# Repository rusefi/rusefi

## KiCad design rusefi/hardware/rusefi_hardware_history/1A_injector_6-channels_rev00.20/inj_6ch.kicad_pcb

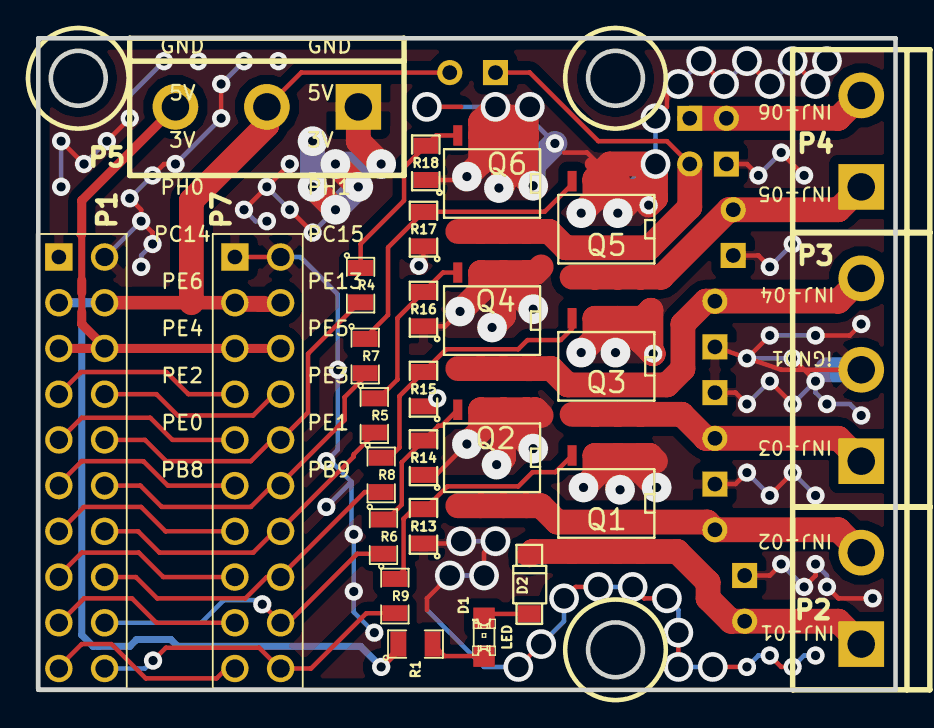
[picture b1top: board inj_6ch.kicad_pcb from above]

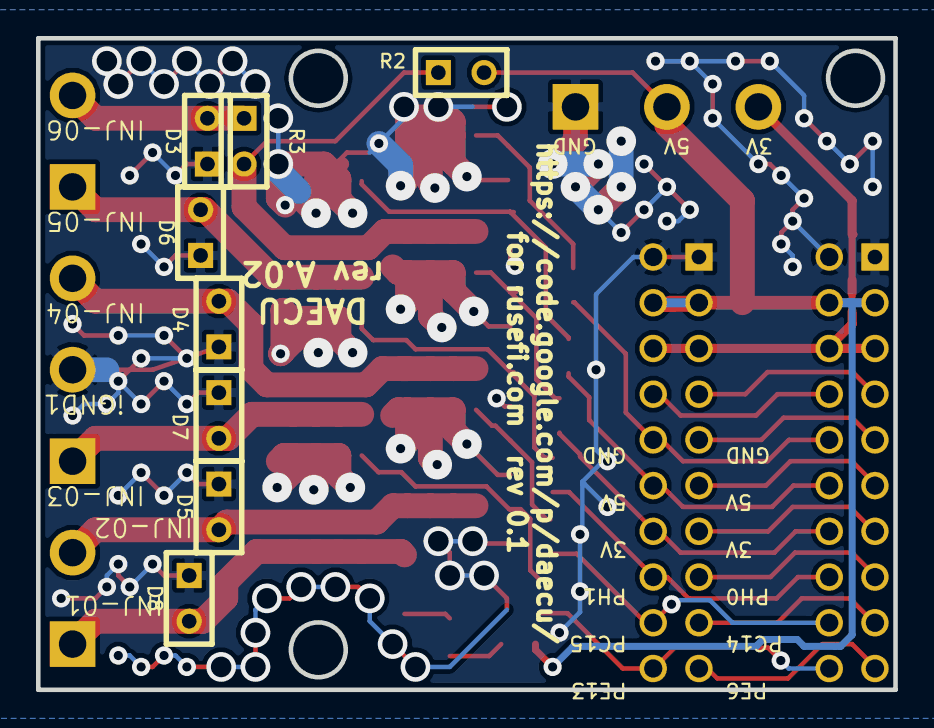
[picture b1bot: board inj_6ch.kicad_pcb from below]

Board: 2 copper layers, 47.6 x 36.2 mm, 35 parts (8 on the bottom side), 32 nets.

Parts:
D1: LED; LED-0805
D2: DIODE; SOD-123
D3, D4, D5, D6, D7, D8: DIODE; SIL-2
P1, P7: CONN_10X2; pin_array_10x2
P2, P4: CONN_2; bornier2
P3, P5: CONN_3; bornier3
Q1, Q2, Q3, Q4, Q5, Q6: OVP_DRIVER; SO8E_ST
R1, R13, R14, R15, R16, R17, R18: 1K; SM0805
R2: OPT; SIL-2
R3: 0R; SIL-2
R4, R5, R6, R7, R8, R9: 20R; SM0805

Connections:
/3V: P1.5, P1.6, P5.3, P7.5, P7.6
/5V: P1.3, P1.4, P5.2, P7.3, P7.4, R1.1, R2.2
/INJ-01: D2.2, D8.2, P2.1, Q1.2
/INJ-01_5V: P1.20, P7.20, R9.2
/INJ-02: D5.2, P2.2, Q2.2
/INJ-02_5V: P1.18, P7.18, R6.2
/INJ-03: D7.2, P3.1, Q3.2
/INJ-03_5V: P1.16, P7.16, R8.2
/INJ-04: D4.2, P3.3, Q4.2
/INJ-04_5V: P1.14, P7.14, R5.2
/INJ-05: D6.2, P4.1, Q5.2
/INJ-05_5V: P1.12, P7.12, R7.2
/INJ-06: Q6.2, R2.1, R3.2
/INJ-06_2: D3.2, P4.2, R3.1
/INJ-06_5V: P1.10, P7.10, R4.2
/PB8: P1.19, P7.19
/PC14: P1.9, P7.9
/PE0: P1.17, P7.17
/PE2: P1.15, P7.15
/PE4: P1.13, P7.13
/PE6: P1.11, P7.11
/PH0: P1.7, P7.7
/PH1: P1.8, P7.8
GND: D3.1, D4.1, D5.1, D6.1, D7.1, D8.1, P1.1, P1.2, P3.2, P5.1, P7.1, P7.2, Q1.3, Q2.3, Q3.3, Q4.3, Q5.3, Q6.3, R13.1, R14.1, R15.1, R16.1, R17.1, R18.1
unnamed: D1.1, R1.2
unnamed: D1.2, D2.1
unnamed: Q6.1, R4.1, R18.2
unnamed: Q4.1, R5.1, R16.2
unnamed: Q3.1, R8.1, R15.2
unnamed: Q2.1, R6.1, R14.2
unnamed: Q1.1, R9.1, R13.2
unnamed: Q5.1, R7.1, R17.2

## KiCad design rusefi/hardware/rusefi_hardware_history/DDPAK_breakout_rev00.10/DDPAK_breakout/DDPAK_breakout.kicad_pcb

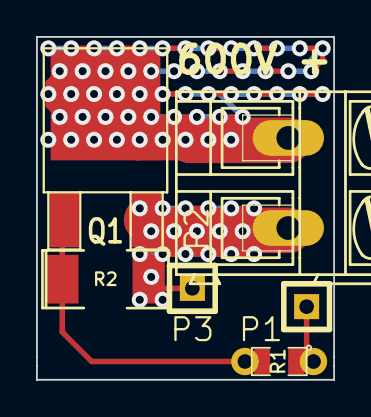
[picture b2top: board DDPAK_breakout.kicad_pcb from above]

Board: 2 copper layers, 16.5 x 19.1 mm, 6 parts (0 on the bottom side), 4 nets.

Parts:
P1, P3: CONN_1; SIL-1
P2: CONN_2; AK300-2
Q1: IRGS14C40L; DPAK2
R1: 1K; SM0805_jumper
R2: 100K; SM2010

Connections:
/GND: P2.2, P3.1, Q1.3, R2.2
/HV: P2.1, Q1.2
/SIG: P1.1, R1.1
/SIG2: Q1.1, R1.2, R2.1

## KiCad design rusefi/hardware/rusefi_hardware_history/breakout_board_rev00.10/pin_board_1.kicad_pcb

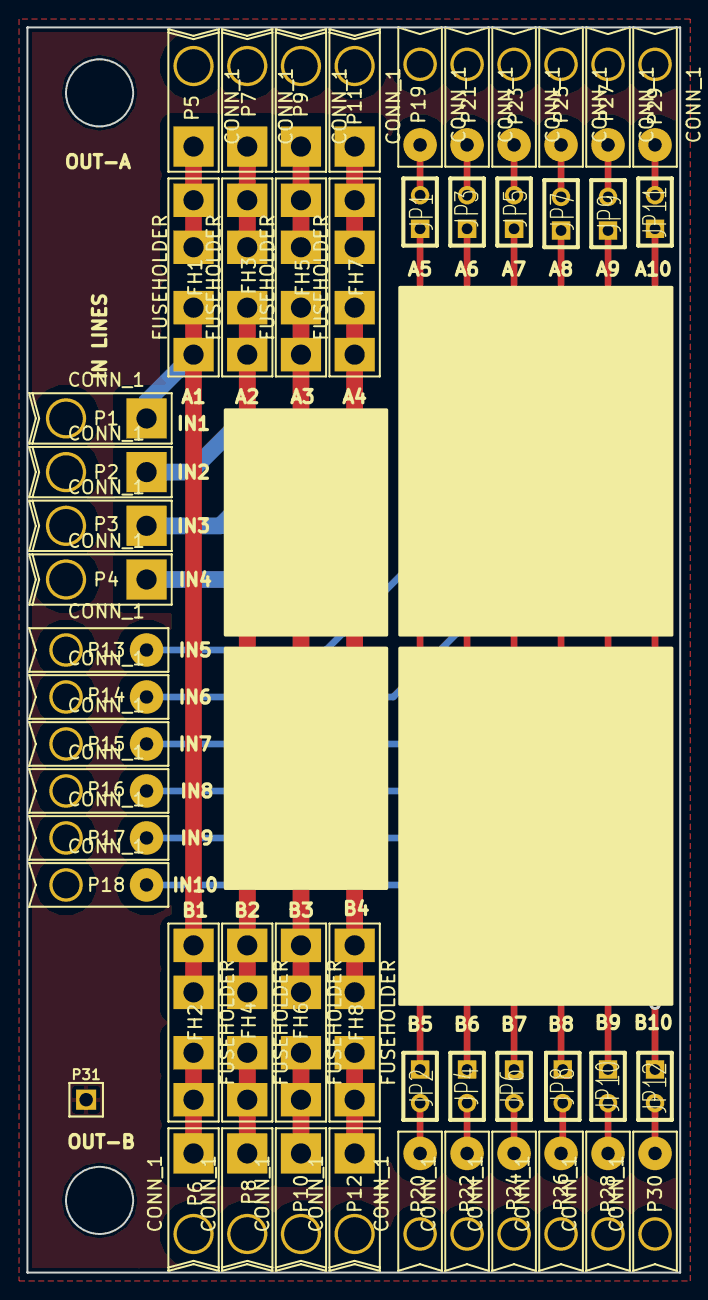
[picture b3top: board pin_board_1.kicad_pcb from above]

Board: 2 copper layers, 49.4 x 94.2 mm, 51 parts (0 on the bottom side), 30 nets.

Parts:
FH1, FH2, FH3, FH4, FH5, FH6, FH7, FH8: FUSEHOLDER
JP1, JP2, JP3, JP4, JP5, JP6, JP7, JP8, JP9, JP10, JP11, JP12: JUMPER; JUMPER-2
P1, P2, P3, P4, P5, P6, P7, P8, P9, P10, P11, P12: CONN_1; PIN_1_16AWG
P13, P14, P15, P16, P17, P18, P19, P20, P21, P22, P23, P24, P25, P26, P27, P28, P29, P30: CONN_1; PIN_1_20AWG
P31: CONN_1; PIN_ARRAY_1

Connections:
unnamed: JP8.2, P26.1
unnamed: JP7.2, P25.1
unnamed: JP7.1, JP8.1, P16.1
unnamed: JP3.2, P21.1
unnamed: JP4.2, P22.1
unnamed: JP3.1, JP4.1, P14.1
unnamed: JP5.1, JP6.1, P15.1
unnamed: JP6.2, P24.1
unnamed: JP5.2, P23.1
unnamed: JP11.2, P29.1
unnamed: JP12.2, P30.1
unnamed: JP11.1, JP12.1, P18.1
unnamed: JP10.2, P28.1
unnamed: JP9.2, P27.1
unnamed: JP9.1, JP10.1, P17.1
unnamed: JP1.2, P19.1
unnamed: JP2.2, P20.1
unnamed: FH3.1, FH4.1, P2.1
unnamed: FH4.2, P8.1
unnamed: FH3.2, P7.1
unnamed: FH1.1, FH2.1, P1.1
unnamed: FH2.2, P6.1
unnamed: FH1.2, P5.1
unnamed: JP1.1, JP2.1, P13.1
unnamed: FH7.1, FH8.1, P4.1
unnamed: FH8.2, P12.1
unnamed: FH7.2, P11.1
unnamed: FH5.1, FH6.1, P3.1
unnamed: FH6.2, P10.1
unnamed: FH5.2, P9.1

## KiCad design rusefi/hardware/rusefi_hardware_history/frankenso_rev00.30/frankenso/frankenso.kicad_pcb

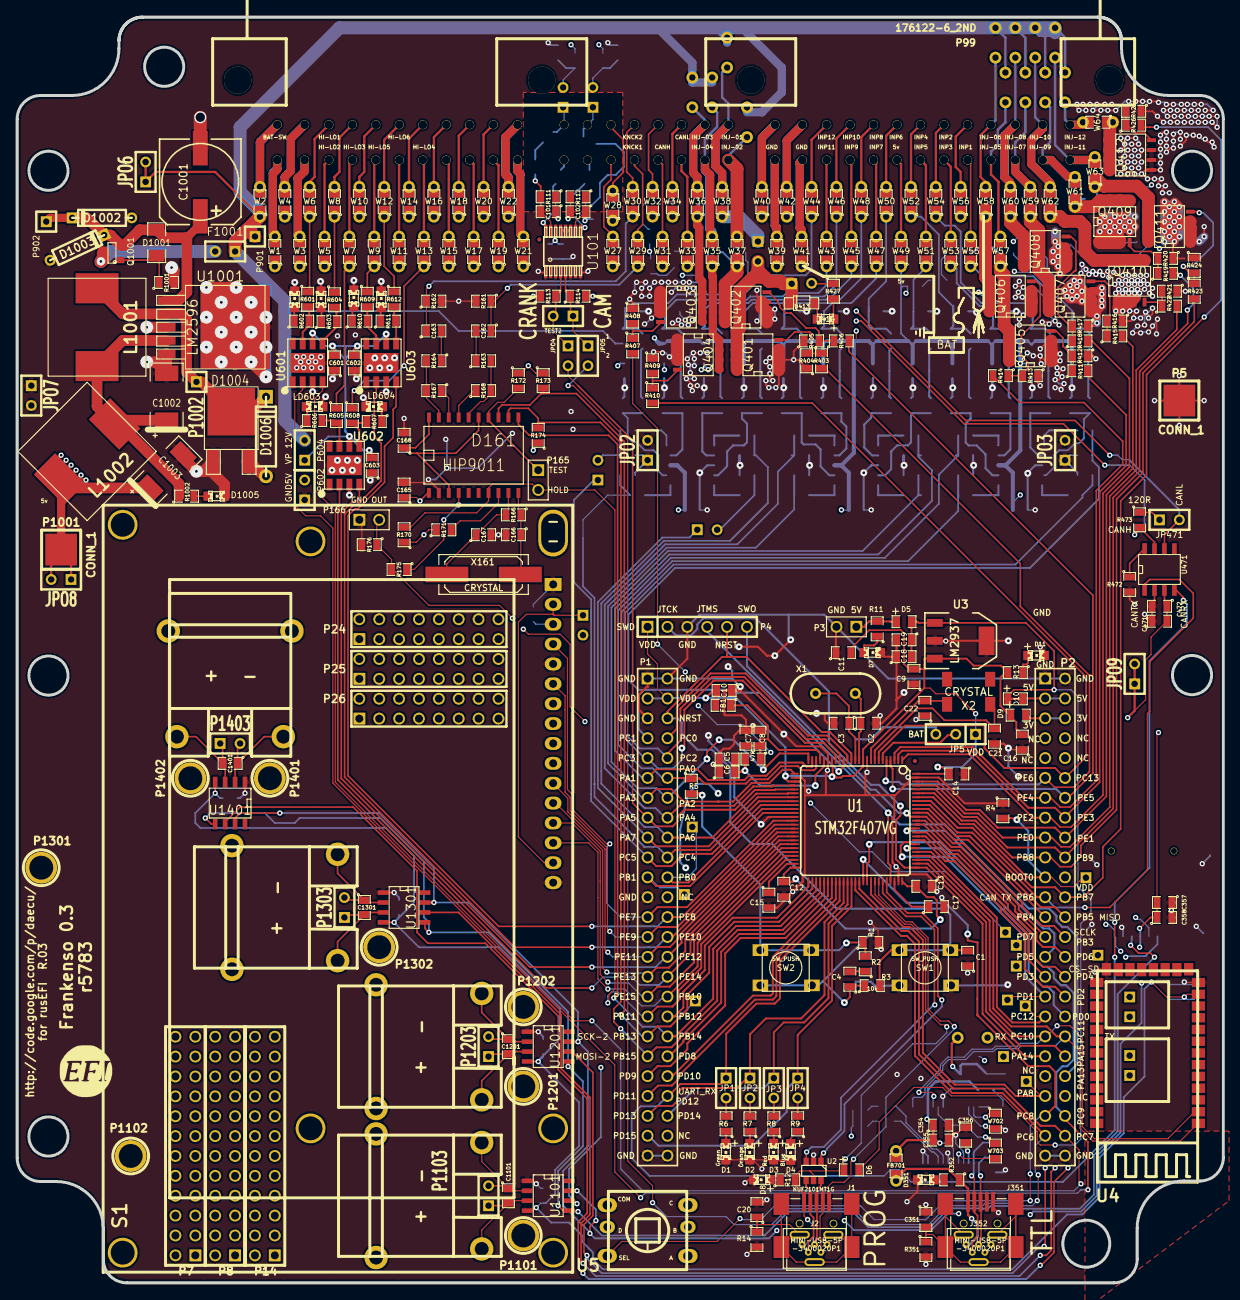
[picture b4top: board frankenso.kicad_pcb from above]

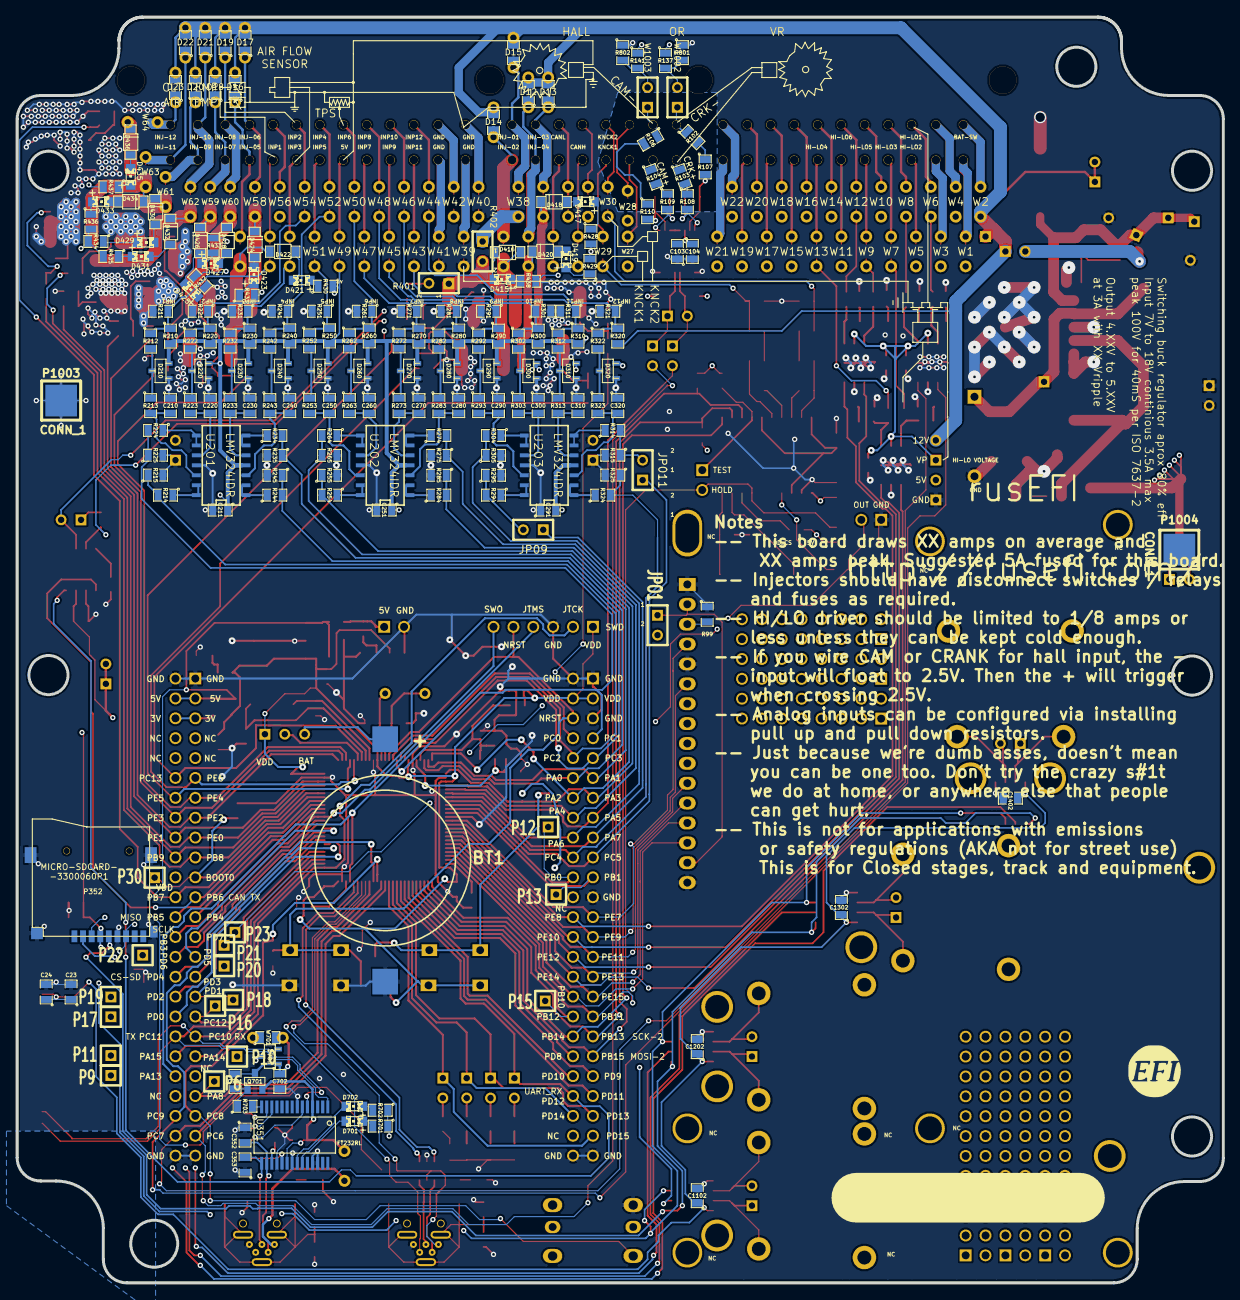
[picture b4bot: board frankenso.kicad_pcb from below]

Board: 4 copper layers, 154.1 x 161.7 mm, 516 parts (209 on the bottom side), 357 nets.

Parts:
BT1: BATTERY_CR2032; BATT_CR2032_MPD
C1, C5, C8, C210, C220, C230, C240, C250, C260, C270, C280, C290, C300, C310, C320: 0.01uF; SM0805
C2, C3, C166, C167: 20pF; SM0805
C4, C15, C17: 2u2F; SM0805
C6, C7, C16, C23: 1uF; SM0805
C9, C10, C11, C12, C13, C14, C18, C20, C24, C104, C165, C211, C251, C291, C355, C471, C601, C602, C603, C701, C702: 0.1uF; SM0805
C19, C354, C358, C472: 4.7uF; SM0805
C21, C22: 12.5pF; SM0805
C101, C102: 1000pF; SM0805
C103: 10uF; SM0805
C162, C163: .047uF; SM0805
C168: .022uF; SM0805
C351: 4700pF; SM0805
C352, C353: 47pF; SM0805
C356, C357: .1uF; SM0805
C1001: 470uF 25V; SMDSVP10
C1002, C1003: 220uF 16V; SM2512
C1101, C1201, C1301, C1401: 10nF; SM0805-SM0603
C1102, C1202, C1302, C1402: 100nF; SM0805-SM0603
D1, D7, D8, D11, D351, D701, D702: LED-grn; LED-0805_A
D2: LED-org; LED-0805_A
D3, D414, D415, D417, D419, D421, D423, D425, D427, D429, D431, D433, D435: LED-red; LED-0805_A
D4: LED-blu; LED-0805_A
D5, D6, D9, D10: DIODESCH; SM0805-diode
D12, D13, D14, D15, D16, D17, D18, D19, D20, D21, D22, D23: DIODESCH; SM0805_jumper
D161: HIP9011; SO20L
D210, D220, D230, D240, D250, D260, D270, D280, D290, D300, D310, D320, D703: DOUBLE_SCHOTTKY; sot23
D413, D416, D418, D420, D422, D424, D426, D428, D430, D432, D434, D436: DIODE; SOD-123
D1001: ZENERSMALL; SM1206
D1002, D1003: TVS; D3
D1004: SCHDPAK; DPAK2
D1005: LED-grn; LED-0805
D1006: DIODESCH; D4
F1001: 3.5A; SIL-2
FB1: FILTER; SM0805
FB701: FILTER; SM0805_jumper
G1: LOGO; LOGO_F
G2: LOGO
J1, J351: MINI-USB-5P-3400020P1
J2, J352: MINI-USB-5P-3400020P1V; MINI-USB_RCTP_V-T_B
JP1, JP2, JP3, JP4, JP471: JUMPER; JUMPER-2
JP5: JUMPER3; SIL-3
JP09, JP011: TEST-AN; SIL-2
JPO1: TEST-LCD; SIL-2
JPO2, JPO3, JPO6, JPO7, JPO8, JPO9: TEST-gnd; SIL-2
JPO4: TEST-CRK; SIL-2
JPO5: TEST-CAM; SIL-2
L1001, L1002: 38uH; SM100uH
LD601, LD602, LD603, LD604, LD605, LD606: LED-blu; LED-0805
P1, P2: CONN_25X2; PIN_ARRAY_25x2_A
P3: CONN_2; PIN_ARRAY_2_A
P4: CONN_6; PIN_ARRAY-6X1
P5, P1001, P1003, P1004: CONN_1; 1PIN_SMD
P6, P9, P10, P11, P12, P13, P15, P16, P17, P18, P19, P20, P21, P22, P23, P30, P901, P902, P1002: CONN_1; SIL-1
P7, P8, P14: CONN_12X2; pin_array_12x2
P24, P25, P26: CONN_8X2; pin_array_8x2
P99: 176122-6_2ND; 176122-6_2nd
P165, P166: CONN_2; PIN_ARRAY_2X1
P352: MICRO-SDCARD-CONNECTOR-3300060P1
P602, P604, P1103, P1203, P1303, P1403: CONN_2; SIL-2
P1101, P1102, P1201, P1202, P1301, P1302, P1401, P1402: CONN_1; 1pin
P1104, P1204, P1304, P1404: CONN_2; tcpl_PCC-SMP
Q401, Q402, Q403, Q404, Q405, Q406, Q407, Q408, Q409, Q410, Q411, Q412: OVP_DRIVER; SO8E_ST
Q701, Q1001: MOS_PRO; SOT23
R1, R3, R4, R113, R114, R163, R164, R175, R176, R212, R222, R232, R242, R252, R262, R272, R282, R292, R302, R312, R321, R322, R472: 10k; SM0805
R2: 100R; SM0805
R5: 330R; SM0805
R6, R7, R8, R9: 680R; SM0805
R10: 47R; SM0805
R11, R12, R13, R352, R701, R702, R703, R1001, R1002: 1k; SM0805
R14: 100k; SM0805
R99: 2K; SM0805
R102, R103, R104, R106, R107, R108, R109, R110, R111, R112: 5k; SM0805
R137, R141, R170, R171, R172, R173, R174, R404, R405, R408, R409, R412, R413, R416, R417, R420, R421, R424, R425, R427, R428, R429, R430, R431, R432, R433, R434, R435, R436, R437, R438: 1K; SM0805
R161, R162, R166, R351: 1M; SM0805
R167, R168: 68k; SM0805
R210, R220, R230, R240, R250, R260, R270, R280, R290, R300, R310, R602, R603, R606, R607, R610, R611: 2700; SM0805
R211, R221, R231, R241, R251, R261, R271, R281, R291, R301, R311: 500K; SM0805
R213, R223, R233, R243, R253, R263, R273, R283, R293, R303, R313, R323, R601, R604, R605, R608, R609, R612: 100; SM0805
R214, R215, R224, R225, R234, R235, R244, R245, R254, R255, R264, R265, R274, R275, R284, R285, R294, R295, R304, R305, R314, R315, R324, R325: 1500; SM0805
R320: 39k; SM0805
R401: OPT; SIL-2
R402: 0R; SIL-2
R403, R406, R407, R410, R411, R414, R415, R418, R419, R422, R423, R426: 20R; SM0805
R473: 120; SM0805
R801, R802: 0R; SM0805
S1: DISPLAY_BL; DISPLAY_4x20_BL
SW1, SW2: SW_PUSH; TL-1105
TEST2: TEST-C-C; SIL-2
U1: STM32F407VG; TQFP_100
U2: NUF2101MT1G; SOT-457
U3: LM2937; SOT223
U4: ITEAD_HC-0X; ITEAD_HC-05
U5: SKQUCAA010
U101: MAX9926/9927; maxim-10-QSOP16
U201, U202, U203: LMV324IDR; SO14N
U351: FT232RL; ssop-28
U471: SN65HVD230; SO8E
U601, U602, U603: TC4427; SOIC8-DFN
U1001: LM2596; DPAK5
U1101, U1201, U1301, U1401: MAX31855KASA; SO8E
W1, W2, W3, W4, W5, W6, W7, W8, W9, W10, W11, W12, W13, W14, W15, W16, W17, W18, W19, W20, W21, W22, W27, W28, W29, W30, W31, W32, W33, W34, W35, W36, W37, W38, W39, W40, W41, W42, W43, W44, W45, W46, W47, W48, W49, W50, W51, W52, W53, W54, W55, W56, W57, W58, W59, W60, W61, W62, W63, W64, W701: TEST; SM0805_jumper
W702, W703: TEST; SM0805
W1002, W1003: JMP; SIL-2
X1: CRYSTAL; HC-49V
X2: CRYSTAL; MC-306
X161: CRYSTAL; Q_49U3HMS

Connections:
/DD_HIP9011/5V: C18.2, C19.1, C103.2, C104.1, C165.1, C211.1, C251.1, C291.2, C1003.1, D5.2, D6.2, D10.1, D10.2, D161.1, D210.3, D220.3, D230.3, D240.3, D250.3, D260.3, D270.3, D280.3, D290.3, D300.3, D310.3, D320.3, D703.2, JPO1.2, JPO8.1, JPO8.2, L1002.2, P2.3, P2.4, P602.2, P1001.1, P1004.1, R113.1, R114.2, R137.1, R141.1, R170.1, R171.1, R172.1, R173.1, R174.1, R210.2, R220.2, R230.2, R240.2, R250.2, R260.2, R270.2, R280.2, R290.2, R300.2, R310.2, R401.2, R427.1, R428.2, R429.2, R430.2, R431.2, R432.2, R433.2, R434.2, R435.2, R436.2, R437.2, R438.2, R701.1, R702.1, U3.1, U101.14, U201.4, U202.4, U203.4, W49.1, W701.1
/DD_HIP9011/CS: D161.8, R171.2
/DD_HIP9011/INT/HLD: D161.7, P1.35, P165.2, R170.2, U1.48
/DD_HIP9011/INTOUT: D161.4, R175.1
/DD_HIP9011/KNOCK1: C162.1, R161.1, W29.1
/DD_HIP9011/KNOCK2: C163.1, R162.1, W30.1
/DD_HIP9011/OUT: P1.8, P166.2, R175.2, R176.1, U1.15
/DD_HIP9011/TEST: D161.14, P165.1, R172.2
/HD44780_VCC: JPO1.1, S1.2, S1.A
/PWR_buck_12V_switcher/FB: C1002.1, L1001.2, L1002.1, R1002.1, U1001.4
/PWR_buck_12V_switcher/OUT: D1004.2, D1006.2, L1001.1, P1002.1, U1001.2
/PWR_buck_12V_switcher/VBAT: C1001.1, D1001.2, D1002.2, D1003.2, P902.1, Q1001.2, U1001.1
/PWR_buck_12V_switcher/Vf: F1001.2, Q1001.3
/adc_amp_divider/INP1: R210.1, R211.1, R212.1, W55.1
/adc_amp_divider/INP2: R220.1, R221.1, R222.1, W54.1
/adc_amp_divider/INP3: R230.1, R231.1, R232.1, W53.1
/adc_amp_divider/INP4: R240.1, R241.1, R242.1, W52.1
/adc_amp_divider/INP5: R250.1, R251.1, R252.1, W51.1
/adc_amp_divider/INP6: R260.1, R261.1, R262.1, W50.1
/adc_amp_divider/INP7: R270.1, R271.1, R272.1, W47.1
/adc_amp_divider/INP8: R280.1, R281.1, R282.1, W48.1
/adc_amp_divider/INP9: R290.1, R291.1, R292.1, W45.1
/adc_amp_divider/INP10: R300.1, R301.1, R302.1, W46.1
/adc_amp_divider/INP11: R310.1, R311.1, R312.1, W43.1
/adc_amp_divider/INP12: R320.1, R321.1, R322.1, W44.1
/adc_amp_divider/OUT1: P1.10, R214.2, R215.1, U1.17
/adc_amp_divider/OUT2: P1.7, R224.2, R225.1, U1.16
/adc_amp_divider/OUT3: P1.12, R5.1, R234.2, R235.1, U1.23
/adc_amp_divider/OUT4: P1.9, R244.2, R245.1, U1.18
/adc_amp_divider/OUT5: P1.14, R254.2, R255.1, U1.25
/adc_amp_divider/OUT6: P1.11, R264.2, R265.1, U1.24
/adc_amp_divider/OUT7: P1.16, R274.2, R275.1, U1.29
/adc_amp_divider/OUT8: P1.13, R284.2, R285.1, U1.26
/adc_amp_divider/OUT9: JP09.1, P1.17, U1.32
/adc_amp_divider/OUT10: P1.18, R304.2, R305.1, U1.31
/adc_amp_divider/OUT11: JP011.1, P1.19, U1.34
/adc_amp_divider/OUT12: P1.20, R324.2, R325.1, U1.33
/can_brd_1/3.3V: C23.1, C24.1, C357.2, C358.1, C471.2, C472.1, C1102.1, C1202.1, C1302.1, C1402.1, D9.2, JPO9.1, JPO9.2, P2.5, P2.6, P352.4, U4.12, U471.3, U1101.4, U1201.4, U1301.4, U1401.4
/can_brd_1/CANH: R473.2, U471.7, W33.1
/can_brd_1/CANL: JP471.2, U471.6, W34.1
/can_brd_1/CAN_RX: JP1.1, P1.44, U1.59, U471.4
/can_brd_1/CAN_TX: P2.23, U1.92, U471.1
/cps_vrs_io_1/CAM: JPO5.1, R114.1, TEST2.1, U101.5
/cps_vrs_io_1/CAM+: P99.24, R104.1
/cps_vrs_io_1/CAM-: P99.32, R106.1, W1003.1
/cps_vrs_io_1/CRANK: JPO4.1, R113.2, TEST2.2, U101.4
/cps_vrs_io_1/CRK2+: P99.23, R103.1
/cps_vrs_io_1/CRK2-: P99.31, R102.1, W1002.1
/hi-lo/12V: D12.2, D13.2, D14.2, D15.2, D16.2, D17.2, D18.2, D19.2, D20.2, D21.2, D22.2, D23.2, F1001.1, JPO6.1, JPO6.2, P604.2, P901.1, R320.2, W2.1
/hi-lo/HL1: R601.1, W6.1
/hi-lo/HL2: R604.1, W8.1
/hi-lo/HL3: R605.1, W7.1
/hi-lo/HL4: R608.1, W13.1
/hi-lo/HL5: R609.1, W9.1
/hi-lo/HL6: R612.1, W12.1
/hi-lo/H_IN1: P2.48, U1.64, U601.4
/hi-lo/H_IN2: P1.32, U1.45, U602.2
/hi-lo/H_IN3: P2.46, U1.66, U601.2
/hi-lo/H_IN4: P1.30, U1.43, U602.4
/hi-lo/H_IN5: P1.26, U1.39, U603.4
/hi-lo/H_IN6: P1.28, U1.41, U603.2
/hi-lo/VP: C601.2, C602.2, C603.2, P604.1, U601.6, U602.6, U603.6
/inj_12ch/INJ-01: D413.2, Q401.2, R401.1, R402.2
/inj_12ch/INJ-01_2: R402.1, W38.1
/inj_12ch/INJ-01_5V: P2.11, R403.2, U1.5
/inj_12ch/INJ-02: D416.2, Q402.2, W37.1
/inj_12ch/INJ-02_5V: P2.14, R406.2, U1.4
/inj_12ch/INJ-03: D418.2, Q403.2, W36.1
/inj_12ch/INJ-03_5V: P2.27, P23.1, R407.2, U1.88
/inj_12ch/INJ-04: D420.2, Q404.2, W35.1
/inj_12ch/INJ-04_5V: P2.12, R410.2, U1.7
/inj_12ch/INJ-05: D422.2, Q405.2, W57.1
/inj_12ch/INJ-05_5V: P2.16, R411.2, U1.2
/inj_12ch/INJ-06: D424.2, Q406.2, W58.1
/inj_12ch/INJ-06_5V: P2.13, R414.2, U1.3
/inj_12ch/INJ-07: D426.2, Q407.2, W59.1
/inj_12ch/INJ-07_5V: P2.18, R415.2, U1.98
/inj_12ch/INJ-08: D428.2, Q408.2, W60.1
/inj_12ch/INJ-08_5V: P2.15, R418.2, U1.1
/inj_12ch/INJ-09: D430.2, Q409.2, W61.1
/inj_12ch/INJ-09_5V: P2.20, R419.2, U1.96
/inj_12ch/INJ-10: D432.2, Q410.2, W62.1
/inj_12ch/INJ-10_5V: P2.17, R422.2, U1.97
/inj_12ch/INJ-11: D434.2, Q411.2, W63.1
/inj_12ch/INJ-11_5V: P2.19, R423.2, U1.95
/inj_12ch/INJ-12: D436.2, Q412.2, W64.1
/inj_12ch/INJ-12_5V: P2.24, R426.2, U1.93
/mmc_usb_1/CB2: U351.13, W702.1
/mmc_usb_1/CB4: U351.12, W702.2
/mmc_usb_1/CS_SD_MODULE: P2.32, P352.2, U1.85
/mmc_usb_1/D+: C353.2, J351.3, J352.3, U351.15
/mmc_usb_1/D-: C352.2, J351.2, J352.2, U351.16
/mmc_usb_1/FTVCC: C354.1, C355.2, FB701.2, Q701.2, U351.4, U351.20
/mmc_usb_1/PWREN#: R703.2, U351.14
/mmc_usb_1/RESET: U351.19, W703.2
/mmc_usb_1/RI: U351.6, W703.1
/mmc_usb_1/Vbus: FB701.1, J351.1, J352.1, R352.1
/mmc_usb_1/shield: C351.2, J351.6, J352.6, R351.1
/stm32f407_board/BOOT0: P2.21, P30.1, R4.2, U1.94
/stm32f407_board/D+: J1.3, J2.3, U2.6
/stm32f407_board/D-: J1.2, J2.2, U2.4
/stm32f407_board/NRST: C1.2, P1.6, P4.5, R3.2, SW1.1, U1.14
/stm32f407_board/PA5: JPO4.2, P1.15, U1.30
/stm32f407_board/PA9: D6.1, J1.1, J2.1, R12.2, U1.68, U2.5
/stm32f407_board/PA10: J1.4, J2.4, U1.69
/stm32f407_board/PA11: U1.70, U2.3
/stm32f407_board/PA12: U1.71, U2.1
/stm32f407_board/PA15: P2.40, P11.1, U1.77
/stm32f407_board/PB0: P1.22, P12.1, U1.35
/stm32f407_board/PB1: P1.21, P13.1, U1.36
/stm32f407_board/PB3: P2.28, P4.6, P352.5, U1.89, U1101.5, U1201.5, U1301.5, U1401.5
/stm32f407_board/PB5: P2.26, P352.3, U1.91
/stm32f407_board/PB10: P1.34, S1.14, U1.47
/stm32f407_board/PB13: D161.13, P1.37, R173.2, U1.52
/stm32f407_board/PB14: D161.11, P1.38, U1.53
/stm32f407_board/PB15: D161.12, P1.39, R174.2, U1.54
/stm32f407_board/PC6: JPO5.2, P2.47, U1.63
/stm32f407_board/PC8: P2.45, U1.65, U5.6
/stm32f407_board/PC10: P2.37, U1.78, U4.2, U351.5
/stm32f407_board/PC11: P2.38, U1.79, U4.1, U351.1
/stm32f407_board/PC12: P2.35, P16.1, U1.80
/stm32f407_board/PD0: P2.36, P17.1, U1.81
/stm32f407_board/PD1: P2.33, P18.1, U1.82
/stm32f407_board/PD2: P2.34, P19.1, U1.83
/stm32f407_board/PD3: P2.31, P20.1, U1.84
/stm32f407_board/PD5: P2.29, P21.1, U1.86
/stm32f407_board/PD6: P2.30, P22.1, U1.87
/stm32f407_board/PD8: P1.40, U1.55, U5.1
/stm32f407_board/PD9: P1.41, U1.56, U5.3
/stm32f407_board/PD10: P1.42, U1.57, U5.2
/stm32f407_board/PD11: P1.43, U1.58, U5.5
/stm32f407_board/PD13: JP2.1, P1.45, U1.60
/stm32f407_board/PD14: JP3.1, P1.46, U1.61
/stm32f407_board/PD15: JP4.1, P1.47, U1.62
/stm32f407_board/PE7: P1.25, S1.4, U1.38
/stm32f407_board/PE9: P1.27, S1.6, U1.40
/stm32f407_board/PE11: P1.29, S1.11, U1.42
/stm32f407_board/PE13: P1.31, S1.12, U1.44
/stm32f407_board/PE15: P1.33, S1.13, U1.46
/stm32f407_board/VDD: C4.1, C9.2, C10.2, C11.2, C12.2, C13.2, C14.2, C16.2, D9.1, FB1.2, JP5.1, P1.3, P1.4, P4.1, R3.1, R13.2, SW2.2, U1.11, U1.19, U1.28, U1.50, U1.75, U1.100, U3.3
/stm32f407_board/shield: C20.1, J1.6, J2.6, R14.1
/thermocouple1//CS: P1.36, P15.1, U1.51, U1101.6
/thermocouple1/MISO: P2.25, P352.7, U1.90, U1101.7, U1201.7, U1301.7, U1401.7
/thermocouple1/TCPL+: C1101.2, P1103.1, P1104.2, U1101.3
/thermocouple1/TCPL-: C1101.1, P1103.2, P1104.1, U1101.2
/thermocouple2//CS: P2.39, P4.2, P10.1, U1.76, U1201.6
/thermocouple2/TCPL+: C1201.2, P1203.1, P1204.2, U1201.3
/thermocouple2/TCPL-: C1201.1, P1203.2, P1204.1, U1201.2
/thermocouple3//CS: P2.43, P6.1, U1.67, U1301.6
/thermocouple3/TCPL+: C1301.2, P1303.1, P1304.2, U1301.3
/thermocouple3/TCPL-: C1301.1, P1303.2, P1304.1, U1301.2
/thermocouple4//CS: P2.42, P4.4, P9.1, U1.72, U1401.6
/thermocouple4/TCPL+: C1401.2, P1403.1, P1404.2, U1401.3
/thermocouple4/TCPL-: C1401.1, P1403.2, P1404.1, U1401.2
GND: BT1.2, C1.1, C2.2, C3.2, C5.1, C6.1, C7.1, C8.1, C9.1, C10.1, C11.1, C12.1, C13.1, C14.1, C15.2, C16.1, C17.2, C18.1, C19.2, C20.2, C21.1, C22.1, C23.2, C24.2, C103.1, C104.2, C165.2, C166.2, C167.2, C168.2, C210.1, C211.2, C220.1, C230.1, C240.1, C250.1, C251.2, C260.1, C270.1, C280.1, C290.1, C291.1, C300.1, C310.1, C320.1, C351.1, C352.1, C353.1, C354.2, C355.1, C356.1, C357.1, C358.2, C471.1, C472.2, C601.1, C602.1, C603.1, C702.2, C1001.2, C1002.2, C1003.2, C1102.2, C1202.2, C1302.2, C1402.2, D1.2, D2.2, D3.2, D4.2, D7.2, D8.2, D11.2, D161.2, D210.1, D220.1, D230.1, D240.1, D250.1, D260.1, D270.1, D280.1, D290.1, D300.1, D310.1, D320.1, D351.2, D1002.1, D1003.1, D1004.1, D1004.3, D1005.2, D1006.1, J1.5, J2.5, J351.5, J352.5, JPO2.1, JPO2.2, JPO3.1, JPO3.2, JPO7.1, JPO7.2, LD601.2, LD602.2, LD603.2, LD604.2, LD605.2, LD606.2, P1.1, P1.2, P1.5, P1.23, P1.49, P1.50, P2.1, P2.2, P2.49, P2.50, P3.2, P4.3, P5.1, P166.1, P352.6, P352.G1, P352.G2, P352.G3, P352.G4, P602.1, P1003.1, Q401.3, Q402.3, Q403.3, Q404.3, Q405.3, Q406.3, Q407.3, Q408.3, Q409.3, Q410.3, Q411.3, Q412.3, R1.2, R4.1, R14.2, R99.1, R161.2, R162.2, R176.2, R211.2, R215.2, R221.2, R225.2, R231.2, R235.2, R241.2, R245.2, R251.2, R255.2, R261.2, R265.2, R271.2, R275.2, R281.2, R285.2, R291.2, R295.2, R301.2, R305.2, R311.2, R315.2, R321.2, R325.2, R351.2, R404.1, R405.1, R408.1, R409.1, R412.1, R413.1, R416.1, R417.1, R420.1, R421.1, R424.1, R425.1, R472.2, R801.1, R802.1, R1001.2, S1.1, S1.5, S1.K, SW1.2, U1.10, U1.20, U1.27, U1.37, U1.74, U1.99, U2.2, U3.2, U3.4, U4.13, U4.21, U4.22, U5.4, U101.1, U101.3, U101.6, U101.8, U101.11, U101.12, U101.13, U201.11, U202.11, U203.11, U351.7, U351.18, U351.21, U351.25, U351.26, U471.2, U601.3, U601.9, U602.3, U602.9, U603.3, U603.9, U1001.3, U1001.5, U1101.1, U1201.1, U1301.1, U1401.1, W39.1, W40.1, W41.1, W42.1
unnamed: P99.12, W2.2
unnamed: P99.35, W32.2
unnamed: D12.1, P99.29, W35.2
unnamed: D15.1, P99.38, W38.2
unnamed: P99.28, W33.2
unnamed: D13.1, P99.37, W36.2
unnamed: P99.27, W31.2
unnamed: P99.36, W34.2
unnamed: P99.26, W29.2
unnamed: P99.25, W27.2
unnamed: P99.34, W30.2
unnamed: P99.33, W28.2
unnamed: D14.1, P99.30, W37.2
unnamed: D21.1, P99.63, W62.2
unnamed: D20.1, P99.50, W61.2
unnamed: D19.1, P99.62, W60.2
unnamed: D22.1, P99.51, W63.2
unnamed: D18.1, P99.49, W59.2
unnamed: D17.1, P99.61, W58.2
unnamed: D16.1, P99.48, W57.2
unnamed: P99.60, W56.2
unnamed: P99.47, W55.2
unnamed: R99.2, S1.3
unnamed: D23.1, P99.64, W64.2
unnamed: P99.40, W41.2
unnamed: P99.42, W45.2
unnamed: P99.54, W44.2
unnamed: P99.41, W43.2
unnamed: P99.53, W42.2
unnamed: P99.55, W46.2
unnamed: P99.52, W40.2
unnamed: P99.39, W39.2
unnamed: P99.59, W54.2
unnamed: P99.46, W53.2
unnamed: P99.58, W52.2
unnamed: P99.45, W51.2
unnamed: P99.57, W50.2
unnamed: P99.44, W49.2
unnamed: P99.56, W48.2
unnamed: P99.43, W47.2
unnamed: P99.19, W16.2
unnamed: P99.11, W21.2
unnamed: P99.22, W22.2
unnamed: P99.21, W20.2
unnamed: P99.18, W14.2
unnamed: P99.20, W18.2
unnamed: P99.10, W19.2
unnamed: P99.9, W17.2
unnamed: P99.8, W15.2
unnamed: P99.13, W4.2
unnamed: P99.2, W3.2
unnamed: P99.1, W1.2
unnamed: P99.3, W5.2
unnamed: P99.7, W13.2
unnamed: P99.17, W12.2
unnamed: P99.6, W11.2
unnamed: P99.16, W10.2
unnamed: P99.5, W9.2
unnamed: P99.15, W8.2
unnamed: P99.4, W7.2
unnamed: P99.14, W6.2
unnamed: D433.1, R436.1
unnamed: D433.2, D434.1
unnamed: D431.1, R435.1
unnamed: D431.2, D432.1
unnamed: D435.2, D436.1
unnamed: D435.1, R437.1
unnamed: D427.1, R433.1
unnamed: D425.2, D426.1
unnamed: D425.1, R432.1
unnamed: D427.2, D428.1
unnamed: D429.2, D430.1
unnamed: D429.1, R434.1
unnamed: Q402.1, R405.2, R406.1
unnamed: D414.1, R427.2
unnamed: D413.1, D414.2
unnamed: D417.1, R428.1
unnamed: D417.2, D418.1
unnamed: D419.2, D420.1
unnamed: D419.1, R429.1
unnamed: D421.2, D422.1
unnamed: D421.1, R430.1
unnamed: D423.2, D424.1
unnamed: D423.1, R431.1
unnamed: D415.2, D416.1
unnamed: D415.1, R438.1
unnamed: Q404.1, R409.2, R410.1
unnamed: Q405.1, R411.1, R412.2
unnamed: Q403.1, R407.1, R408.2
unnamed: Q401.1, R403.1, R404.2
unnamed: Q406.1, R413.2, R414.1
unnamed: Q412.1, R425.2, R426.1
unnamed: Q411.1, R423.1, R424.2
unnamed: Q410.1, R421.2, R422.1
unnamed: Q409.1, R419.1, R420.2
unnamed: Q408.1, R417.2, R418.1
unnamed: Q407.1, R415.1, R416.2
unnamed: JP011.2, R314.2, R315.1
unnamed: R304.1, U203.8, U203.9
unnamed: C290.2, R293.2, U203.12
unnamed: D320.2, R322.2, R323.1
unnamed: D310.2, R312.2, R313.1
unnamed: C320.2, R323.2, U203.3
unnamed: R224.1, U201.8, U201.9
unnamed: D280.2, R282.2, R283.1
unnamed: D270.2, R272.2, R273.1
unnamed: D290.2, R292.2, R293.1
unnamed: D300.2, R302.2, R303.1
unnamed: R264.1, U202.8, U202.9
unnamed: R274.1, U202.6, U202.7
unnamed: R284.1, U202.1, U202.2
unnamed: R254.1, U202.13, U202.14
unnamed: R244.1, U201.1, U201.2
unnamed: R234.1, U201.6, U201.7
unnamed: C230.2, R233.2, U201.5
unnamed: C310.2, R313.2, U203.5
unnamed: R314.1, U203.6, U203.7
unnamed: R324.1, U203.1, U203.2
unnamed: JP09.2, R294.2, R295.1
unnamed: C250.2, R253.2, U202.12
unnamed: C260.2, R263.2, U202.10
unnamed: C280.2, R283.2, U202.3
unnamed: R214.1, U201.13, U201.14
unnamed: D230.2, R232.2, R233.1
unnamed: C220.2, R223.2, U201.10
unnamed: C210.2, R213.2, U201.12
unnamed: C270.2, R273.2, U202.5
unnamed: C240.2, R243.2, U201.3
unnamed: R294.1, U203.13, U203.14
unnamed: C300.2, R303.2, U203.10
unnamed: D250.2, R252.2, R253.1
unnamed: D260.2, R262.2, R263.1
unnamed: D210.2, R212.2, R213.1
unnamed: D220.2, R222.2, R223.1
unnamed: D240.2, R242.2, R243.1
unnamed: C701.2, C702.1, D703.1, Q701.3, W701.2
unnamed: D701.2, U351.23
unnamed: D702.1, R702.2
unnamed: D702.2, U351.22
unnamed: D701.1, R701.2
unnamed: C701.1, Q701.1, R703.1
unnamed: D351.1, R352.2
unnamed: C356.2, U351.17
unnamed: R472.1, U471.8
unnamed: JP471.1, R473.1
unnamed: R104.2, R109.1
unnamed: R103.2, R108.1
unnamed: R102.2, R107.1
unnamed: C102.1, R110.2, R112.1, U101.10
unnamed: R106.2, R110.1
unnamed: C102.2, R109.2, R112.2, U101.9
unnamed: C101.2, R107.2, R111.2, U101.15
unnamed: C101.1, R108.2, R111.1, U101.16
unnamed: R137.2, R801.2, W1002.2
unnamed: R141.2, R802.2, W1003.2
unnamed: R601.2, R602.2, U601.7
unnamed: R603.2, R604.2, U601.5
unnamed: R605.2, R606.2, U602.7
unnamed: LD603.1, R606.1
unnamed: LD605.1, R610.1
unnamed: R609.2, R610.2, U603.7
unnamed: R611.2, R612.2, U603.5
unnamed: LD606.1, R611.1
unnamed: R607.2, R608.2, U602.5
unnamed: LD602.1, R603.1
unnamed: LD604.1, R607.1
unnamed: LD601.1, R602.1
unnamed: C163.2, R164.1
unnamed: D161.17, R168.1
unnamed: D161.16, R163.2, R168.2
unnamed: D161.19, R164.2, R167.2
unnamed: D161.18, R167.1
unnamed: C162.2, R163.1
unnamed: C168.1, D161.3, D161.15, D161.20
unnamed: C167.1, D161.9, R166.2, X161.1
unnamed: C166.1, D161.10, R166.1, X161.2
unnamed: D1001.1, Q1001.1, R1001.1
unnamed: D1005.1, R1002.2
unnamed: C22.2, U1.9, X2.1
unnamed: C21.2, U1.8, X2.2
unnamed: C2.1, U1.12, X1.2
unnamed: D1.1, R6.1
unnamed: D2.1, R7.1
unnamed: D3.1, R8.1
unnamed: D4.1, R9.1
unnamed: D7.1, R11.1
unnamed: D8.1, R12.1
unnamed: D11.1, R13.1
unnamed: D5.1, P3.1, R11.2
unnamed: BT1.1, JP5.3
unnamed: JP5.2, U1.6
unnamed: JP4.2, R9.2
unnamed: JP3.2, R8.2
unnamed: JP2.2, R7.2
unnamed: JP1.2, R6.2
unnamed: R1.1, R2.2, R5.2, SW2.1
unnamed: C5.2, C6.2, R10.2, U1.21
unnamed: C3.1, U1.13, X1.1
unnamed: C17.1, U1.73
unnamed: C15.1, U1.49
unnamed: C4.2, R2.1
unnamed: C7.2, C8.2, FB1.1, R10.1, U1.22

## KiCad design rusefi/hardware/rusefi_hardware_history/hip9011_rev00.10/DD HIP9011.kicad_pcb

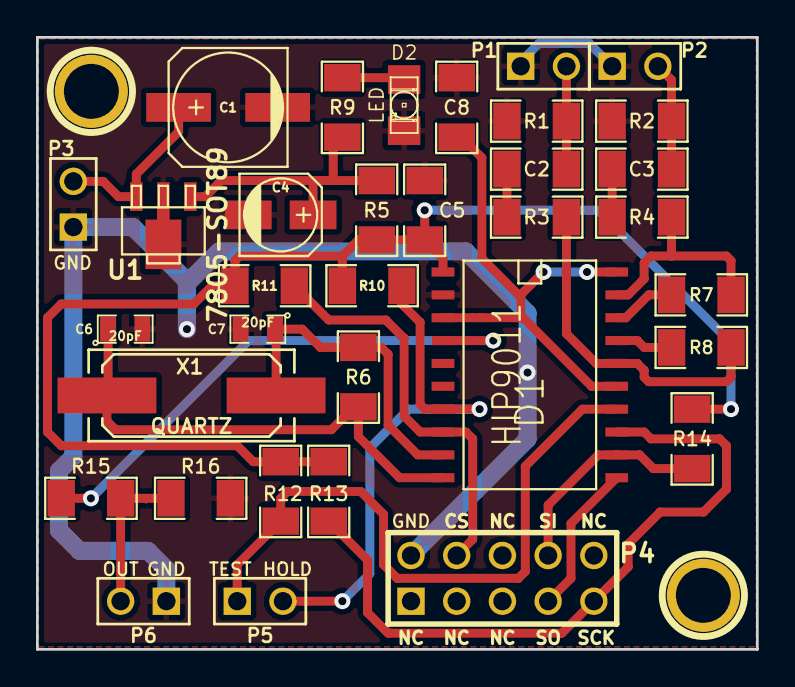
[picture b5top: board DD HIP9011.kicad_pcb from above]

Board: 2 copper layers, 40.0 x 34.0 mm, 35 parts (1 on the bottom side), 24 nets.

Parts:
C1: 100u; c_elec_6.3x5.3
C2, C3: 47n; SM1206
C4: 10u; c_elec_4x5.3
C5: 100n; SM1206
C6, C7: 20pF; SM0805
C8: 22n; SM1206
D1: HIP9011; SO20L
D2: LED; LED-1206
G1: LOGO; LOGO_F
P1: KNOCK 1; PIN_ARRAY_2X1
P2: KNOCK 2; PIN_ARRAY_2X1
P3: 12V; PIN_ARRAY_2X1
P4: CONN_5X2; PIN_ARRAY_5x2
P5, P6: CONN_2; PIN_ARRAY_2X1
R1, R2, R6: 1M; SM1206
R3, R4, R15, R16: 10k; SM1206
R5: 10R; SM1206
R7, R8: 68k; SM1206
R9: 470R; SM1206
R10, R11, R12, R13, R14: 1K; SM1206
U1: 7805-SOT89; sot89
X1: QUARTZ; Q_49U3HMS

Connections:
/+5V: C5.1, D1.1, R5.2, R10.1, R11.1, R12.1, R13.1, R14.1
/+12V: C1.1, P3.2, U1.3
/CS: D1.8, P4.4, R11.2
/GND: C1.2, C4.2, C5.2, C6.2, C7.2, C8.2, D1.2, D2.2, P1.1, P2.1, P3.1, P4.2, P6.1, R1.2, R2.2, R16.2, U1.2
/INT/HLD: D1.7, P5.2, R10.2
/INTOUT: D1.4, R15.1
/OUT: P6.2, R15.2, R16.1
/SCK: D1.13, P4.9, R13.2
/SI: D1.12, P4.8, R14.2
/SO: D1.11, P4.7
/TEST: D1.14, P5.1, R12.2
unnamed: D2.1, R9.1
unnamed: C4.1, R5.1, R9.2, U1.1
unnamed: C7.1, D1.9, R6.2, X1.2
unnamed: C3.1, P2.2, R2.1
unnamed: C3.2, R4.1
unnamed: C6.1, D1.10, R6.1, X1.1
unnamed: C8.1, D1.3, D1.15, D1.20
unnamed: D1.16, R3.2, R8.2
unnamed: D1.17, R8.1
unnamed: D1.18, R7.1
unnamed: D1.19, R4.2, R7.2
unnamed: C2.2, R3.1
unnamed: C2.1, P1.2, R1.1

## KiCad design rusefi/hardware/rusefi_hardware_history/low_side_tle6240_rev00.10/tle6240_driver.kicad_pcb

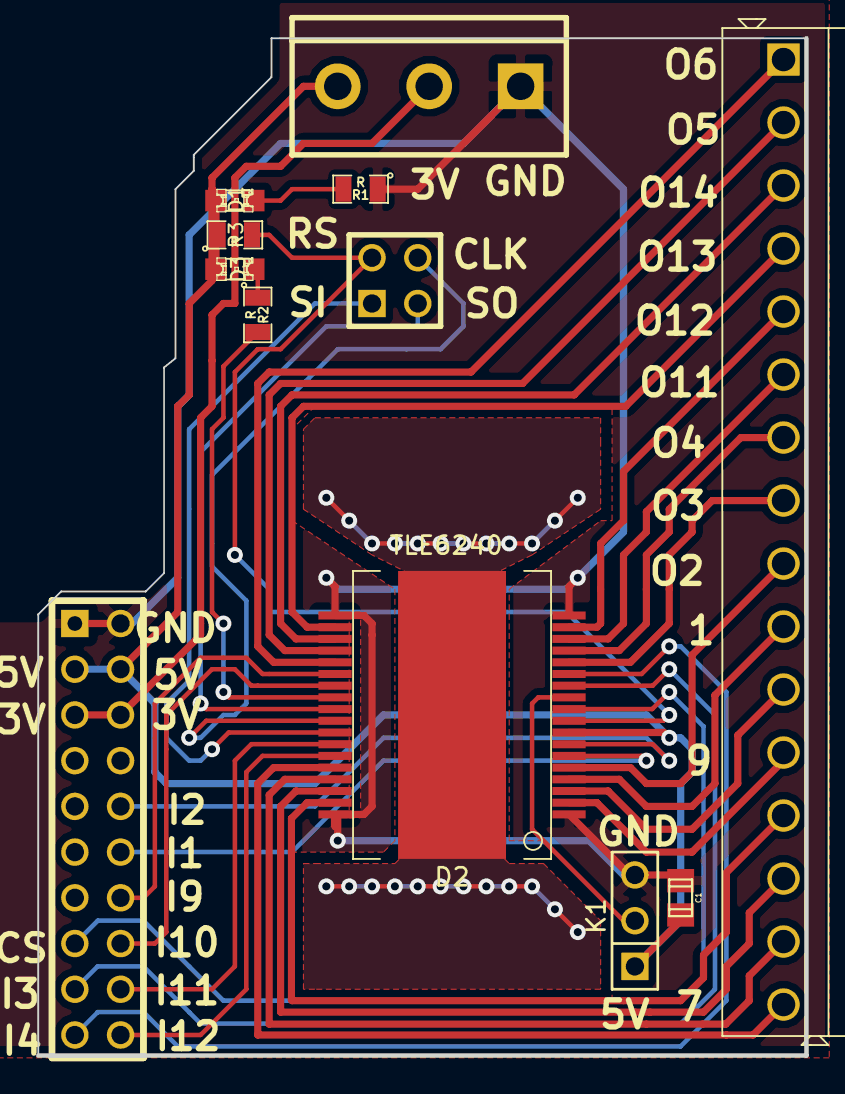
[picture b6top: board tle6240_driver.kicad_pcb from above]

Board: 2 copper layers, 42.7 x 56.5 mm, 12 parts (0 on the bottom side), 36 nets.

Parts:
C1: C; c_0805
D1, D3: LED; LED-0805
D2: TLE6240; PG-DSO-36
K1: JUMPER3; PIN_ARRAY_3X1
K2: CONN_3; bornier3
P1: CONN_10X2; PIN_ARRAY_10X2
P2: CONN_16; SIL-16_3.5MM
P3: CONN_2X2; PIN_ARRAY_2X2
R1, R2, R3: R; SM0805

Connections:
+5V: C1.1, D1.1, D2.8, D3.1, K1.1, K2.3, P1.3, P1.4, R3.1
/+3.3V: K2.2, P1.5, P1.6
/CS: D2.10, P1.15
/Fault: D2.26, R2.2
/IN1: D2.6, P1.12
/IN2: D2.7, P1.10
/IN3: D2.12, P1.17
/IN4: D2.13, P1.19
/IN9: D2.24, P1.14
/IN10: D2.25, P1.16
/IN11: D2.30, P1.18
/IN12: D2.31, P1.20
/OUT1: D2.4, P2.10
/OUT2: D2.5, P2.9
/OUT3: D2.14, P2.8
/OUT4: D2.15, P2.7
/OUT5: D2.22, P2.2
/OUT6: D2.23, P2.1
/OUT7: D2.32, P2.16
/OUT8: D2.33, P2.15
/OUT9: D2.2, P2.12
/OUT10: D2.3, P2.11
/OUT11: D2.16, P2.6
/OUT12: D2.17, P2.5
/OUT13: D2.20, P2.4
/OUT14: D2.21, P2.3
/OUT15: D2.34, P2.14
/OUT16: D2.35, P2.13
/PRG: D2.11, K1.2
/Reset: D2.9, P3.2, R3.2
/SCLK: D2.28, P3.4
/SI: D2.29, P3.1
/SO: D2.27, P3.3
GND: C1.2, D2.1, D2.18, D2.19, D2.36, K1.3, K2.1, P1.1, P1.2, R1.1
unnamed: D3.2, R2.1
unnamed: D1.2, R1.2

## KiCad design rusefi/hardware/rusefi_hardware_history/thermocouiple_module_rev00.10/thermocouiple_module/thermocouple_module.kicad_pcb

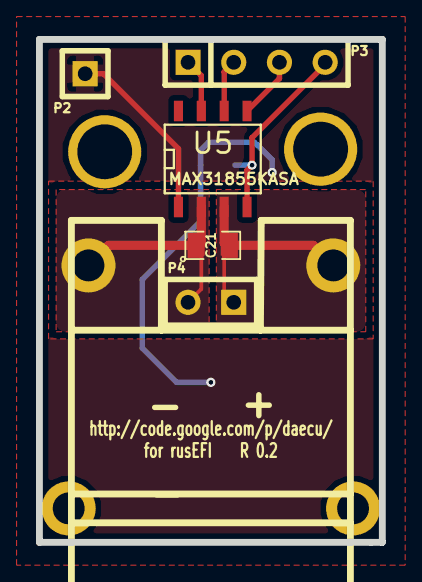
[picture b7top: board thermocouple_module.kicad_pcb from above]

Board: 2 copper layers, 19.0 x 27.9 mm, 9 parts (1 on the bottom side), 7 nets.

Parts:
C8: 100nF; SM0805-SM0603
C21: 10nF; SM0805-SM0603
P1: CONN_2; tcpl_PCC-SMP
P2: CONN_1; SIL-1
P3: CONN_4; SIL-4
P4: CONN_2; SIL-2
U5: MAX31855KASA; SO8E
V801, V802: VIA; 1pin

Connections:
3.3v: C8.1, P3.4, U5.4
//CS: P3.2, U5.6
/MISO: P3.1, U5.7
/SCK: P3.3, U5.5
/TCPL+: C21.2, P1.2, P4.1, U5.3
/TCPL-: C21.1, P1.1, P4.2, U5.2
GND: C8.2, P2.1, U5.1
